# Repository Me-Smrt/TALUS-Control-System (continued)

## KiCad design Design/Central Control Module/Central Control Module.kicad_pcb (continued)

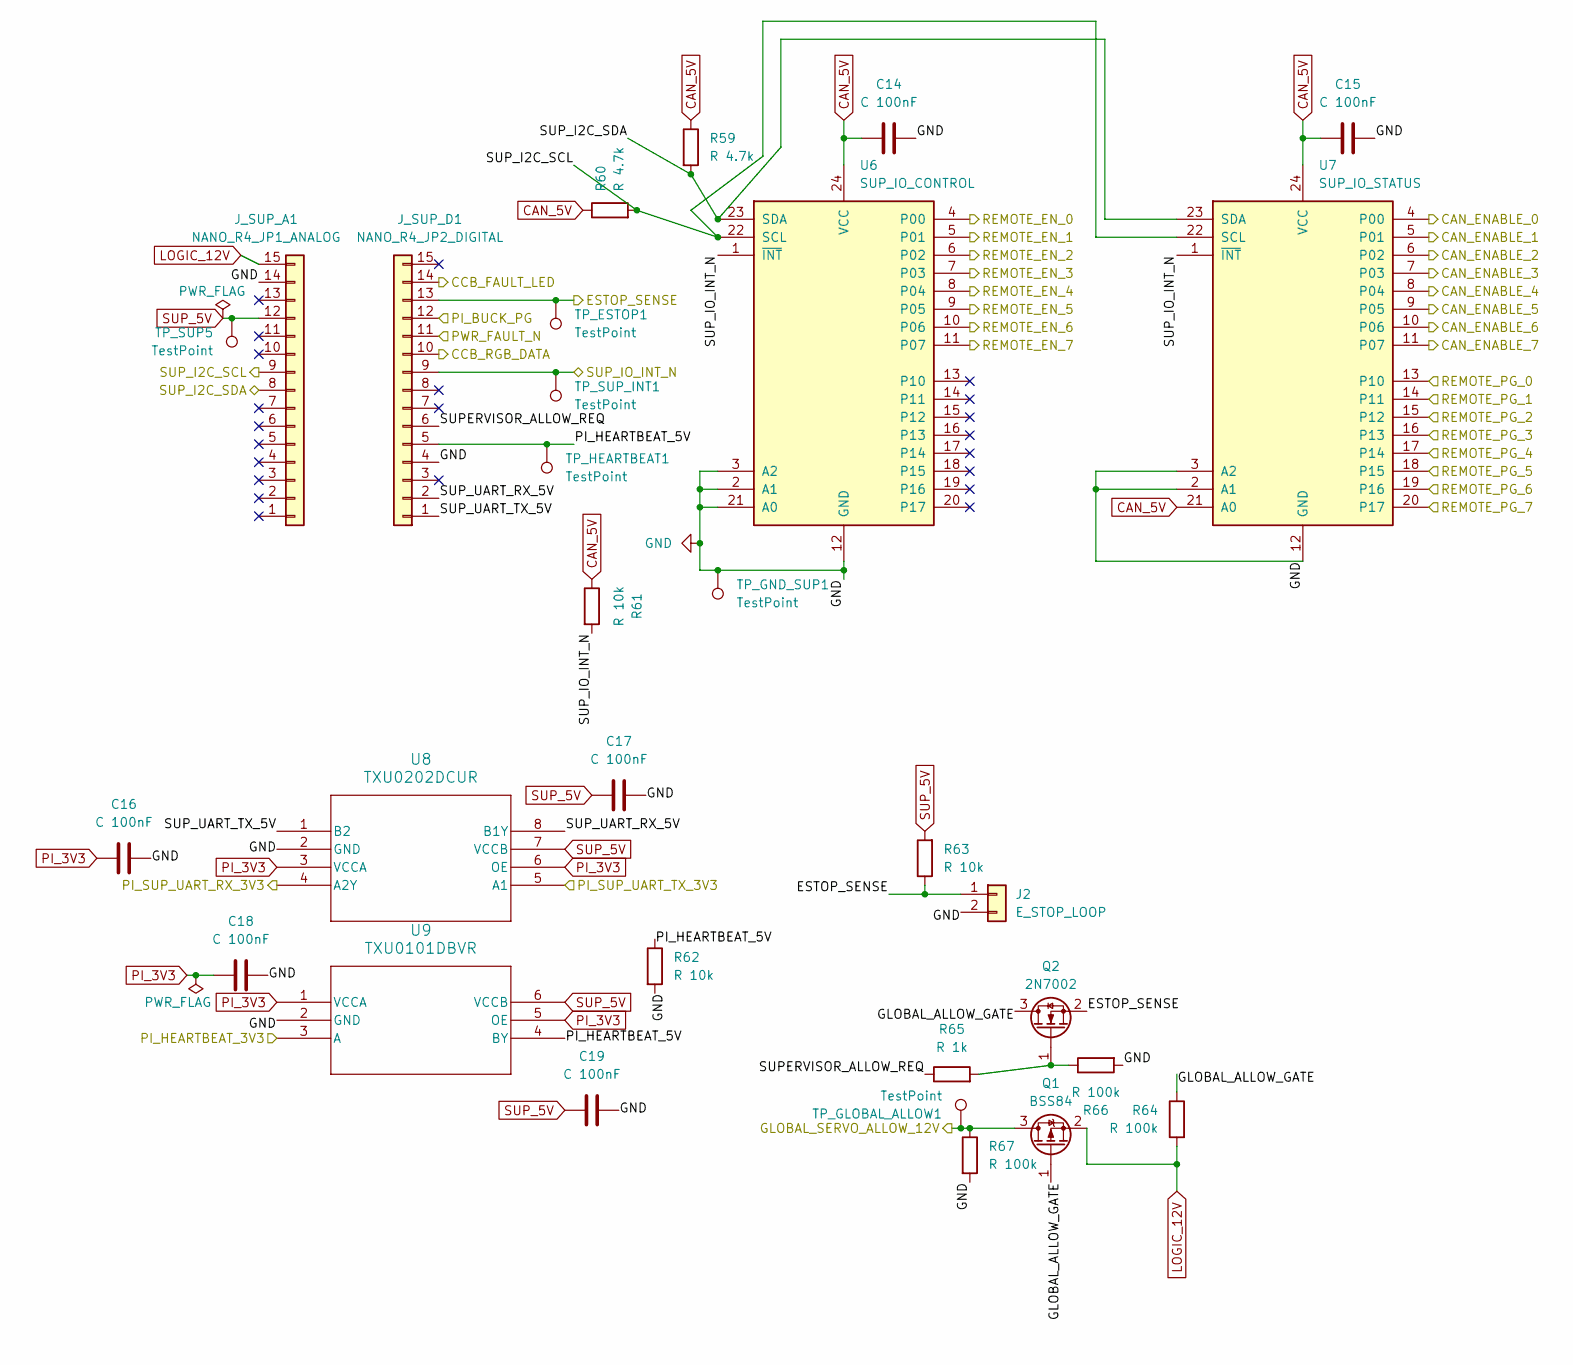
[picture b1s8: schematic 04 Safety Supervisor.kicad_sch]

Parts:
C14, C15, C16, C17, C18, C19: C 100nF; C_0603_1608Metric; MPN GRM188R72A104KA35D
J2: E_STOP_LOOP; PinHeader_1x02_P2.54mm_Vertical; MPN TSW-102-07-G-S
J_SUP_A1: NANO_R4_JP1_ANALOG; PinSocket_1x15_P2.54mm_Vertical; MPN SSW-115-01-S-S
J_SUP_D1: NANO_R4_JP2_DIGITAL; PinSocket_1x15_P2.54mm_Vertical; MPN SSW-115-01-S-S
Q1: BSS84; SOT-23; MPN BSS84LT1G
Q2: 2N7002; SOT-23; MPN 2N7002LT1G
R59, R60: R 4.7k; R_0603_1608Metric; MPN RC0603FR-074K7L
R61, R62, R63: R 10k; R_0603_1608Metric; MPN RC0603FR-0710KL
R64, R66, R67: R 100k; R_0603_1608Metric; MPN RC0603FR-07100KL
R65: R 1k; R_0603_1608Metric; MPN RC0603FR-071KL
TP_ESTOP1: TestPoint; TestPoint_Pad_D1.5mm
TP_GLOBAL_ALLOW1: TestPoint; TestPoint_Pad_D1.5mm
TP_GND_SUP1: TestPoint; TestPoint_Pad_D1.5mm
TP_HEARTBEAT1: TestPoint; TestPoint_Pad_D1.5mm
TP_SUP5: TestPoint; TestPoint_Pad_D1.5mm
TP_SUP_INT1: TestPoint; TestPoint_Pad_D1.5mm
U6: SUP_IO_CONTROL; TSSOP-24_4.4x7.8mm_P0.65mm; MPN TCA9535PWR
U7: SUP_IO_STATUS; TSSOP-24_4.4x7.8mm_P0.65mm; MPN TCA9535PWR
U8: TXU0202DCUR; MPN TXU0202DCUR
U9: TXU0101DBVR; MPN TXU0101DBVR

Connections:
/01 PI Interface/PI_HEARTBEAT_3V3: U9.3 (A); also elsewhere on the board
/01 PI Interface/PI_SUP_UART_RX_3V3: U8.4 (A2Y); also elsewhere on the board
/01 PI Interface/PI_SUP_UART_TX_3V3: U8.5 (A1); also elsewhere on the board
/01 PI Interface/PWR_FAULT_N: J_SUP_D1.11; also elsewhere on the board
/02 Logic Power/PI_BUCK_PG: J_SUP_D1.12; also elsewhere on the board
/04 Safety Supervisor/CCB_FAULT_LED: J_SUP_D1.14; also elsewhere on the board
/04 Safety Supervisor/CCB_RGB_DATA: J_SUP_D1.10; also elsewhere on the board
/04 Safety Supervisor/ESTOP_SENSE: J2.1, J_SUP_D1.13, Q2.2 (S), R63.1, TP_ESTOP1.1 (1_1); also elsewhere on the board
/04 Safety Supervisor/GLOBAL_ALLOW_GATE: Q1.1 (G), Q2.3 (D), R64.1
/04 Safety Supervisor/PI_HEARTBEAT_5V: J_SUP_D1.5, R62.1, TP_HEARTBEAT1.1 (1_1), U9.4 (BY)
/04 Safety Supervisor/REMOTE_EN_0: U6.4 (P00); also elsewhere on the board
/04 Safety Supervisor/REMOTE_EN_1: U6.5 (P01); also elsewhere on the board
/04 Safety Supervisor/REMOTE_EN_2: U6.6 (P02); also elsewhere on the board
/04 Safety Supervisor/REMOTE_EN_3: U6.7 (P03); also elsewhere on the board
/04 Safety Supervisor/REMOTE_EN_4: U6.8 (P04); also elsewhere on the board
/04 Safety Supervisor/REMOTE_EN_5: U6.9 (P05); also elsewhere on the board
/04 Safety Supervisor/REMOTE_EN_6: U6.10 (P06); also elsewhere on the board
/04 Safety Supervisor/REMOTE_EN_7: U6.11 (P07); also elsewhere on the board
/04 Safety Supervisor/REMOTE_PG_0: U7.13 (P10); also elsewhere on the board
/04 Safety Supervisor/REMOTE_PG_1: U7.14 (P11); also elsewhere on the board
/04 Safety Supervisor/REMOTE_PG_2: U7.15 (P12); also elsewhere on the board
/04 Safety Supervisor/REMOTE_PG_3: U7.16 (P13); also elsewhere on the board
/04 Safety Supervisor/REMOTE_PG_4: U7.17 (P14); also elsewhere on the board
/04 Safety Supervisor/REMOTE_PG_5: U7.18 (P15); also elsewhere on the board
/04 Safety Supervisor/REMOTE_PG_6: U7.19 (P16); also elsewhere on the board
/04 Safety Supervisor/REMOTE_PG_7: U7.20 (P17); also elsewhere on the board
/04 Safety Supervisor/SUPERVISOR_ALLOW_REQ: J_SUP_D1.6, R65.1
/04 Safety Supervisor/SUP_I2C_SCL: J_SUP_A1.9, R60.2, U6.22 (SCL), U7.22 (SCL); also elsewhere on the board
/04 Safety Supervisor/SUP_I2C_SDA: J_SUP_A1.8, R59.2, U6.23 (SDA), U7.23 (SDA); also elsewhere on the board
/04 Safety Supervisor/SUP_IO_INT_N: J_SUP_D1.9, R61.2, TP_SUP_INT1.1 (1_1), U6.1 (~INT), U7.1 (~INT); also elsewhere on the board
/04 Safety Supervisor/SUP_UART_RX_5V: J_SUP_D1.2, U8.8 (B1Y)
/04 Safety Supervisor/SUP_UART_TX_5V: J_SUP_D1.1, U8.1 (B2)
/08 Remote_Interfaces/GLOBAL_SERVO_ALLOW_12V: Q1.3 (D), R67.1, TP_GLOBAL_ALLOW1.1 (1_1); also elsewhere on the board
/CAN_ENABLE_0: U7.4 (P00); also elsewhere on the board
/CAN_ENABLE_1: U7.5 (P01); also elsewhere on the board
/CAN_ENABLE_2: U7.6 (P02); also elsewhere on the board
/CAN_ENABLE_3: U7.7 (P03); also elsewhere on the board
/CAN_ENABLE_4: U7.8 (P04); also elsewhere on the board
/CAN_ENABLE_5: U7.9 (P05); also elsewhere on the board
/CAN_ENABLE_6: U7.10 (P06); also elsewhere on the board
/CAN_ENABLE_7: U7.11 (P07); also elsewhere on the board
CAN_5V: C14.1, C15.1, R59.1, R60.1, R61.1, U6.24 (VCC), U7.21 (A0), U7.24 (VCC); also elsewhere on the board
GND: C14.2, C15.2, C16.2, C17.2, C18.2, C19.2, J2.2, J_SUP_A1.14, J_SUP_D1.4, R62.2, R66.2, R67.2, TP_GND_SUP1.1 (1_1), U6.2 (A1), U6.3 (A2), U6.12 (GND), U6.21 (A0), U7.2 (A1), U7.3 (A2), U7.12 (GND), U8.2 (GND), U9.2 (GND); also elsewhere on the board
LOGIC_12V: J_SUP_A1.15, Q1.2 (S), R64.2; also elsewhere on the board
unnamed: Q2.1 (G), R65.2, R66.1
PI_3V3: C16.1, C18.1, U8.3 (VCCA), U8.6 (OE), U9.1 (VCCA), U9.5 (OE); also elsewhere on the board
SUP_5V: C17.1, C19.1, J_SUP_A1.12, R63.2, TP_SUP5.1 (1_1), U8.7 (VCCB), U9.6 (VCCB); also elsewhere on the board

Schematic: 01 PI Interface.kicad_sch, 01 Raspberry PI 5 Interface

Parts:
C1: C 100 nF; C_0603_1608Metric; MPN GRM188R72A104KA35D
JP1: EEPROM_WP; SolderJumper-2_P1.3mm_Open_Pad1.0x1.5mm
J_PI1: Raspberry PI 5 GPIO; PinSocket_2x20_P2.54mm_Vertical_RPi5; MPN SSW-120-01-S-D
R1, R2: R 3.9 kΩ; R_0603_1608Metric; MPN RC0603FR-073K9L
R3: R 1 kΩ; R_0603_1608Metric; MPN RC0603FR-071KL
U1: CAT24C32WI-GT3; SOIC-8_3.9x4.9mm_P1.27mm; MPN CAT24C32WI-GT3

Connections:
/01 PI Interface/CS0_N: J_PI1.24; also elsewhere on the board
/01 PI Interface/CS1_N: J_PI1.26; also elsewhere on the board
/01 PI Interface/CS2_N: J_PI1.7; also elsewhere on the board
/01 PI Interface/CS3_N: J_PI1.11; also elsewhere on the board
/01 PI Interface/CS4_N: J_PI1.13; also elsewhere on the board
/01 PI Interface/CS5_N: J_PI1.15; also elsewhere on the board
/01 PI Interface/CS6_N: J_PI1.16; also elsewhere on the board
/01 PI Interface/CS7_N: J_PI1.18; also elsewhere on the board
/01 PI Interface/EEPROM_WP: JP1.1 (A), R3.2, U1.7 (WP)
/01 PI Interface/ID_SC: J_PI1.28, R2.2, U1.6 (SCL)
/01 PI Interface/ID_SD: J_PI1.27, R1.2, U1.5 (SDA)
/01 PI Interface/INT0_N: J_PI1.22; also elsewhere on the board
/01 PI Interface/INT1_N: J_PI1.29; also elsewhere on the board
/01 PI Interface/INT2_N: J_PI1.31; also elsewhere on the board
/01 PI Interface/INT3_N: J_PI1.32; also elsewhere on the board
/01 PI Interface/INT4_N: J_PI1.33; also elsewhere on the board
/01 PI Interface/INT5_N: J_PI1.35; also elsewhere on the board
/01 PI Interface/INT6_N: J_PI1.36; also elsewhere on the board
/01 PI Interface/INT7_N: J_PI1.37; also elsewhere on the board
/01 PI Interface/PI_HEARTBEAT_3V3: J_PI1.12; also elsewhere on the board
/01 PI Interface/PI_SUP_UART_RX_3V3: J_PI1.10; also elsewhere on the board
/01 PI Interface/PI_SUP_UART_TX_3V3: J_PI1.8; also elsewhere on the board
/01 PI Interface/PWR_FAULT_N: J_PI1.38; also elsewhere on the board
/01 PI Interface/SPI_MISO: J_PI1.21; also elsewhere on the board
/01 PI Interface/SPI_MOSI: J_PI1.19; also elsewhere on the board
/01 PI Interface/SPI_SCK: J_PI1.23; also elsewhere on the board
GND: C1.2, JP1.2 (B), J_PI1.6, J_PI1.9, J_PI1.14, J_PI1.20, J_PI1.25, J_PI1.30, J_PI1.34, J_PI1.39, U1.1 (A0), U1.2 (A1), U1.3 (A2), U1.4 (GND); also elsewhere on the board
PI_3V3: C1.1, J_PI1.1, J_PI1.17, R1.1, R2.1, R3.1, U1.8 (VCC); also elsewhere on the board
PI_5V: J_PI1.2, J_PI1.4; also elsewhere on the board

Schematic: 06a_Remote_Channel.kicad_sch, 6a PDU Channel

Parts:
C20: C 100 nF / 50 V, X7R; C_0603_1608Metric; MPN GRM188R72A104KA35D
C21: C 1 µF / 50 V, X7R; C_1206_3216Metric; MPN GRM31CR71H105KA61L
C22: C 4.7 nF; C_0603_1608Metric; MPN GRM188R71H472KA01D
C23: C 10 nF / 50 V, X7R; C_0603_1608Metric; MPN GRM188R71H103KA01D
C24: C 100 nF; C_0603_1608Metric; MPN GRM188R72A104KA35D
D12: GREEN_LED; LED_0603_1608Metric; MPN LTST-C190KGKT
R68: R 1 kΩ; R_0603_1608Metric; MPN RC0603FR-071KL
R69: R 100 kΩ; R_0603_1608Metric; MPN RC0603FR-07100KL
R70: R 82 Ω; R_0603_1608Metric; MPN RC0603FR-0782RL
R71: R 10 kΩ; R_0603_1608Metric; MPN RC0603FR-0710KL
R72: R 887 Ω; R_0603_1608Metric; MPN RC0603FR-07887RL
R73: R 10k; R_0603_1608Metric; MPN RC0603FR-0710KL
R137: R 4.7k; R_0603_1608Metric; MPN RC0603FR-074K7L
R145: R 910k; R_0603_1608Metric; MPN RC0603FR-07910KL
R153: R 49.9k; R_0603_1608Metric; MPN RC0603FR-0749K9L
U10: TPS259830ONRGER; PARTREV B

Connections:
/04 Safety Supervisor/REMOTE_EN_0: R68.1; also elsewhere on the board
/04 Safety Supervisor/REMOTE_PG_0: R71.2, U10.13 (PG); also elsewhere on the board
/06 Remote Power PDU/PDU_CH0/REMOTE_IMON_RAW: R72.1, R73.1, U10.9 (IMON)
/06 Remote Power PDU/REMOTE_IMON_0: C24.1, R73.2; also elsewhere on the board
/06 Remote Power PDU/REMOTE_VBUS: C20.2, R145.1, U10.1 (IN), U10.2 (IN__1), U10.3 (IN__2), U10.16 (IN__3), U10.25 (IN__4); also elsewhere on the board
/06 Remote Power PDU/REMOTE_VBUS_0: C21.2, R137.2, U10.17 (OUT), U10.18 (OUT__1), U10.19 (OUT__2), U10.20 (OUT__3), U10.21 (OUT__4), U10.22 (OUT__5), U10.23 (OUT__6), U10.24 (OUT__7); also elsewhere on the board
CAN_5V: R71.1; also elsewhere on the board
GND: C20.1, C21.1, C22.2, C23.1, C24.2, D12.1 (K), R69.2, R70.2, R72.2, R153.2, U10.4 (GND), U10.5 (GND__1), U10.10 (RETRY_DLY), U10.14 (GND__2), U10.26 (GND__3); also elsewhere on the board
unnamed: D12.2 (A), R137.1
unnamed: C23.2, U10.15 (DVDT/BGATE)
unnamed: R68.2, R69.1, U10.6 (EN/UVLO)
unnamed: R70.1, U10.8 (ILIM)
unnamed: C22.1, U10.7 (ITIMER)
unnamed: R145.2, R153.1, U10.12 (OVLO)

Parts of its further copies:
C25, C30, C35, C40, C45, C50, C55: C 4.7 nF; C_0603_1608Metric; MPN GRM188R71H472KA01D
C26, C31, C36, C41, C46, C51, C56: C 100 nF; C_0603_1608Metric; MPN GRM188R72A104KA35D
C27, C32, C37, C42, C47, C52, C57: C 100 nF / 50 V, X7R; C_0603_1608Metric; MPN GRM188R72A104KA35D
C28, C33, C38, C43, C48, C53, C58: C 1 µF / 50 V, X7R; C_1206_3216Metric; MPN GRM31CR71H105KA61L
C29, C34, C39, C44, C49, C54, C59: C 10 nF / 50 V, X7R; C_0603_1608Metric; MPN GRM188R71H103KA01D
D13, D14, D15, D16, D17, D18, D19: GREEN_LED; LED_0603_1608Metric; MPN LTST-C190KGKT
R74, R80, R86, R92, R98, R104, R110: R 1 kΩ; R_0603_1608Metric; MPN RC0603FR-071KL
R75, R81, R87, R93, R99, R105, R111: R 100 kΩ; R_0603_1608Metric; MPN RC0603FR-07100KL
R76, R82, R88, R94, R100, R106, R112: R 82 Ω; R_0603_1608Metric; MPN RC0603FR-0782RL
R77, R83, R89, R95, R101, R107, R113: R 10 kΩ; R_0603_1608Metric; MPN RC0603FR-0710KL
R78, R84, R90, R96, R102, R108, R114: R 10k; R_0603_1608Metric; MPN RC0603FR-0710KL
R79, R85, R91, R97, R103, R109, R115: R 887 Ω; R_0603_1608Metric; MPN RC0603FR-07887RL
R138, R139, R140, R141, R142, R143, R144: R 4.7k; R_0603_1608Metric; MPN RC0603FR-074K7L
R146, R147, R148, R149, R150, R151, R152: R 910k; R_0603_1608Metric; MPN RC0603FR-07910KL
R154, R155, R156, R157, R158, R159, R160: R 49.9k; R_0603_1608Metric; MPN RC0603FR-0749K9L
U11, U12, U13, U14, U15, U16, U17: TPS259830ONRGER; PARTREV B

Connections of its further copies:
/04 Safety Supervisor/REMOTE_EN_1: R74.1; also elsewhere on the board
/04 Safety Supervisor/REMOTE_EN_2: R80.1; also elsewhere on the board
/04 Safety Supervisor/REMOTE_EN_3: R86.1; also elsewhere on the board
/04 Safety Supervisor/REMOTE_EN_4: R92.1; also elsewhere on the board
/04 Safety Supervisor/REMOTE_EN_5: R98.1; also elsewhere on the board
/04 Safety Supervisor/REMOTE_EN_6: R104.1; also elsewhere on the board
/04 Safety Supervisor/REMOTE_EN_7: R110.1; also elsewhere on the board
/04 Safety Supervisor/REMOTE_PG_1: R77.2, U11.13 (PG); also elsewhere on the board
/04 Safety Supervisor/REMOTE_PG_2: R83.2, U12.13 (PG); also elsewhere on the board
/04 Safety Supervisor/REMOTE_PG_3: R89.2, U13.13 (PG); also elsewhere on the board
/04 Safety Supervisor/REMOTE_PG_4: R95.2, U14.13 (PG); also elsewhere on the board
/04 Safety Supervisor/REMOTE_PG_5: R101.2, U15.13 (PG); also elsewhere on the board
/04 Safety Supervisor/REMOTE_PG_6: R107.2, U16.13 (PG); also elsewhere on the board
/04 Safety Supervisor/REMOTE_PG_7: R113.2, U17.13 (PG); also elsewhere on the board
/06 Remote Power PDU/PDU_CH1/REMOTE_IMON_RAW: R78.1, R79.1, U11.9 (IMON)
/06 Remote Power PDU/PDU_CH2/REMOTE_IMON_RAW: R84.1, R85.1, U12.9 (IMON)
/06 Remote Power PDU/PDU_CH3/REMOTE_IMON_RAW: R90.1, R91.1, U13.9 (IMON)
/06 Remote Power PDU/PDU_CH4/REMOTE_IMON_RAW: R96.1, R97.1, U14.9 (IMON)
/06 Remote Power PDU/PDU_CH5/REMOTE_IMON_RAW: R102.1, R103.1, U15.9 (IMON)
/06 Remote Power PDU/PDU_CH6/REMOTE_IMON_RAW: R108.1, R109.1, U16.9 (IMON)
/06 Remote Power PDU/PDU_CH7/REMOTE_IMON_RAW: R114.1, R115.1, U17.9 (IMON)
/06 Remote Power PDU/REMOTE_IMON_1: C26.1, R78.2; also elsewhere on the board
/06 Remote Power PDU/REMOTE_IMON_2: C31.1, R84.2; also elsewhere on the board
/06 Remote Power PDU/REMOTE_IMON_3: C36.1, R90.2; also elsewhere on the board
/06 Remote Power PDU/REMOTE_IMON_4: C41.1, R96.2; also elsewhere on the board
/06 Remote Power PDU/REMOTE_IMON_5: C46.1, R102.2; also elsewhere on the board
/06 Remote Power PDU/REMOTE_IMON_6: C51.1, R108.2; also elsewhere on the board
/06 Remote Power PDU/REMOTE_IMON_7: C56.1, R114.2; also elsewhere on the board
/06 Remote Power PDU/REMOTE_VBUS: C27.2, C32.2, C37.2, C42.2, C47.2, C52.2, C57.2, R146.1, R147.1, R148.1, R149.1, R150.1, R151.1, R152.1, U11.1 (IN), U11.2 (IN__1), U11.3 (IN__2), U11.16 (IN__3), U11.25 (IN__4), U12.1 (IN), U12.2 (IN__1), U12.3 (IN__2), U12.16 (IN__3), U12.25 (IN__4), U13.1 (IN), U13.2 (IN__1), U13.3 (IN__2), U13.16 (IN__3), U13.25 (IN__4), U14.1 (IN), U14.2 (IN__1), U14.3 (IN__2), U14.16 (IN__3), U14.25 (IN__4), U15.1 (IN), U15.2 (IN__1), U15.3 (IN__2), U15.16 (IN__3), U15.25 (IN__4), U16.1 (IN), U16.2 (IN__1), U16.3 (IN__2), U16.16 (IN__3), U16.25 (IN__4), U17.1 (IN), U17.2 (IN__1), U17.3 (IN__2), U17.16 (IN__3), U17.25 (IN__4); also elsewhere on the board
/06 Remote Power PDU/REMOTE_VBUS_1: C28.2, R138.2, U11.17 (OUT), U11.18 (OUT__1), U11.19 (OUT__2), U11.20 (OUT__3), U11.21 (OUT__4), U11.22 (OUT__5), U11.23 (OUT__6), U11.24 (OUT__7); also elsewhere on the board
/06 Remote Power PDU/REMOTE_VBUS_2: C33.2, R139.2, U12.17 (OUT), U12.18 (OUT__1), U12.19 (OUT__2), U12.20 (OUT__3), U12.21 (OUT__4), U12.22 (OUT__5), U12.23 (OUT__6), U12.24 (OUT__7); also elsewhere on the board
/06 Remote Power PDU/REMOTE_VBUS_3: C38.2, R140.2, U13.17 (OUT), U13.18 (OUT__1), U13.19 (OUT__2), U13.20 (OUT__3), U13.21 (OUT__4), U13.22 (OUT__5), U13.23 (OUT__6), U13.24 (OUT__7); also elsewhere on the board
/06 Remote Power PDU/REMOTE_VBUS_4: C43.2, R141.2, U14.17 (OUT), U14.18 (OUT__1), U14.19 (OUT__2), U14.20 (OUT__3), U14.21 (OUT__4), U14.22 (OUT__5), U14.23 (OUT__6), U14.24 (OUT__7); also elsewhere on the board
/06 Remote Power PDU/REMOTE_VBUS_5: C48.2, R142.2, U15.17 (OUT), U15.18 (OUT__1), U15.19 (OUT__2), U15.20 (OUT__3), U15.21 (OUT__4), U15.22 (OUT__5), U15.23 (OUT__6), U15.24 (OUT__7); also elsewhere on the board
/06 Remote Power PDU/REMOTE_VBUS_6: C53.2, R143.2, U16.17 (OUT), U16.18 (OUT__1), U16.19 (OUT__2), U16.20 (OUT__3), U16.21 (OUT__4), U16.22 (OUT__5), U16.23 (OUT__6), U16.24 (OUT__7); also elsewhere on the board
/06 Remote Power PDU/REMOTE_VBUS_7: C58.2, R144.2, U17.17 (OUT), U17.18 (OUT__1), U17.19 (OUT__2), U17.20 (OUT__3), U17.21 (OUT__4), U17.22 (OUT__5), U17.23 (OUT__6), U17.24 (OUT__7); also elsewhere on the board
CAN_5V: R77.1, R83.1, R89.1, R95.1, R101.1, R107.1, R113.1; also elsewhere on the board
GND: C25.2, C26.2, C27.1, C28.1, C29.1, C30.2, C31.2, C32.1, C33.1, C34.1, C35.2, C36.2, C37.1, C38.1, C39.1, C40.2, C41.2, C42.1, C43.1, C44.1, C45.2, C46.2, C47.1, C48.1, C49.1, C50.2, C51.2, C52.1, C53.1, C54.1, C55.2, C56.2, C57.1, C58.1, C59.1, D13.1 (K), D14.1 (K), D15.1 (K), D16.1 (K), D17.1 (K), D18.1 (K), D19.1 (K), R75.2, R76.2, R79.2, R81.2, R82.2, R85.2, R87.2, R88.2, R91.2, R93.2, R94.2, R97.2, R99.2, R100.2, R103.2, R105.2, R106.2, R109.2, R111.2, R112.2, R115.2, R154.2, R155.2, R156.2, R157.2, R158.2, R159.2, R160.2, U11.4 (GND), U11.5 (GND__1), U11.10 (RETRY_DLY), U11.14 (GND__2), U11.26 (GND__3), U12.4 (GND), U12.5 (GND__1), U12.10 (RETRY_DLY), U12.14 (GND__2), U12.26 (GND__3), U13.4 (GND), U13.5 (GND__1), U13.10 (RETRY_DLY), U13.14 (GND__2), U13.26 (GND__3), U14.4 (GND), U14.5 (GND__1), U14.10 (RETRY_DLY), U14.14 (GND__2), U14.26 (GND__3), U15.4 (GND), U15.5 (GND__1), U15.10 (RETRY_DLY), U15.14 (GND__2), U15.26 (GND__3), U16.4 (GND), U16.5 (GND__1), U16.10 (RETRY_DLY), U16.14 (GND__2), U16.26 (GND__3), U17.4 (GND), U17.5 (GND__1), U17.10 (RETRY_DLY), U17.14 (GND__2), U17.26 (GND__3); also elsewhere on the board
unnamed: D13.2 (A), R138.1
unnamed: D14.2 (A), R139.1
unnamed: D15.2 (A), R140.1
unnamed: D16.2 (A), R141.1
unnamed: D17.2 (A), R142.1
unnamed: D18.2 (A), R143.1
unnamed: D19.2 (A), R144.1
unnamed: C29.2, U11.15 (DVDT/BGATE)
unnamed: R74.2, R75.1, U11.6 (EN/UVLO)
unnamed: R76.1, U11.8 (ILIM)
unnamed: C25.1, U11.7 (ITIMER)
unnamed: R146.2, R154.1, U11.12 (OVLO)
unnamed: C34.2, U12.15 (DVDT/BGATE)
unnamed: R80.2, R81.1, U12.6 (EN/UVLO)
unnamed: R82.1, U12.8 (ILIM)
unnamed: C30.1, U12.7 (ITIMER)
unnamed: R147.2, R155.1, U12.12 (OVLO)
unnamed: C39.2, U13.15 (DVDT/BGATE)
unnamed: R86.2, R87.1, U13.6 (EN/UVLO)
unnamed: R88.1, U13.8 (ILIM)
unnamed: C35.1, U13.7 (ITIMER)
unnamed: R148.2, R156.1, U13.12 (OVLO)
unnamed: C44.2, U14.15 (DVDT/BGATE)
unnamed: R92.2, R93.1, U14.6 (EN/UVLO)
unnamed: R94.1, U14.8 (ILIM)
unnamed: C40.1, U14.7 (ITIMER)
unnamed: R149.2, R157.1, U14.12 (OVLO)
unnamed: C49.2, U15.15 (DVDT/BGATE)
unnamed: R98.2, R99.1, U15.6 (EN/UVLO)
unnamed: R100.1, U15.8 (ILIM)
unnamed: C45.1, U15.7 (ITIMER)
unnamed: R150.2, R158.1, U15.12 (OVLO)
unnamed: C54.2, U16.15 (DVDT/BGATE)
unnamed: R104.2, R105.1, U16.6 (EN/UVLO)
unnamed: R106.1, U16.8 (ILIM)
unnamed: C50.1, U16.7 (ITIMER)
unnamed: R151.2, R159.1, U16.12 (OVLO)
unnamed: C59.2, U17.15 (DVDT/BGATE)
unnamed: R110.2, R111.1, U17.6 (EN/UVLO)
unnamed: R112.1, U17.8 (ILIM)
unnamed: C55.1, U17.7 (ITIMER)
unnamed: R152.2, R160.1, U17.12 (OVLO)

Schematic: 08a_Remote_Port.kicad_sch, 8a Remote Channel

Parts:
CR1: PESD2CAN24DBZRQ1; MPN ESD2CAN24DBZRQ1
J3: 0438100003; CONN_SD-43810-011_08_CLIP_MOL; MPN 0438100003
R116: R 1k; R_0603_1608Metric; MPN RC0603FR-071KL

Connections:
/06 Remote Power PDU/REMOTE_VBUS_0: J3.3, J3.5, J3.7; also elsewhere on the board
/08 Remote_Interfaces/GLOBAL_SERVO_ALLOW_12V: R116.1; also elsewhere on the board
/08 Remote_Interfaces/REMOTE_CH0/CAN_H: CR1.1, J3.1; also elsewhere on the board
/08 Remote_Interfaces/REMOTE_CH0/CAN_L: CR1.2, J3.2; also elsewhere on the board
GND: CR1.3, J3.4, J3.6; also elsewhere on the board
unnamed: J3.8, R116.2

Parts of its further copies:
CR2, CR3, CR4, CR5, CR6, CR7, CR8: PESD2CAN24DBZRQ1; MPN ESD2CAN24DBZRQ1
J4, J5, J6, J7, J8, J9, J10: 0438100003; CONN_SD-43810-011_08_CLIP_MOL; MPN 0438100003
R117, R118, R119, R120, R121, R122, R123: R 1k; R_0603_1608Metric; MPN RC0603FR-071KL

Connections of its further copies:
/06 Remote Power PDU/REMOTE_VBUS_1: J4.3, J4.5, J4.7; also elsewhere on the board
/06 Remote Power PDU/REMOTE_VBUS_2: J5.3, J5.5, J5.7; also elsewhere on the board
/06 Remote Power PDU/REMOTE_VBUS_3: J6.3, J6.5, J6.7; also elsewhere on the board
/06 Remote Power PDU/REMOTE_VBUS_4: J7.3, J7.5, J7.7; also elsewhere on the board
/06 Remote Power PDU/REMOTE_VBUS_5: J8.3, J8.5, J8.7; also elsewhere on the board
/06 Remote Power PDU/REMOTE_VBUS_6: J9.3, J9.5, J9.7; also elsewhere on the board
/06 Remote Power PDU/REMOTE_VBUS_7: J10.3, J10.5, J10.7; also elsewhere on the board
/08 Remote_Interfaces/GLOBAL_SERVO_ALLOW_12V: R117.1, R118.1, R119.1, R120.1, R121.1, R122.1, R123.1; also elsewhere on the board
/08 Remote_Interfaces/REMOTE_CH1/CAN_H: CR2.1, J4.1; also elsewhere on the board
/08 Remote_Interfaces/REMOTE_CH1/CAN_L: CR2.2, J4.2; also elsewhere on the board
/08 Remote_Interfaces/REMOTE_CH2/CAN_H: CR3.1, J5.1; also elsewhere on the board
/08 Remote_Interfaces/REMOTE_CH2/CAN_L: CR3.2, J5.2; also elsewhere on the board
/08 Remote_Interfaces/REMOTE_CH3/CAN_H: CR4.1, J6.1; also elsewhere on the board
/08 Remote_Interfaces/REMOTE_CH3/CAN_L: CR4.2, J6.2; also elsewhere on the board
/08 Remote_Interfaces/REMOTE_CH4/CAN_H: CR5.1, J7.1; also elsewhere on the board
/08 Remote_Interfaces/REMOTE_CH4/CAN_L: CR5.2, J7.2; also elsewhere on the board
/08 Remote_Interfaces/REMOTE_CH5/CAN_H: CR6.1, J8.1; also elsewhere on the board
/08 Remote_Interfaces/REMOTE_CH5/CAN_L: CR6.2, J8.2; also elsewhere on the board
/08 Remote_Interfaces/REMOTE_CH6/CAN_H: CR7.1, J9.1; also elsewhere on the board
/08 Remote_Interfaces/REMOTE_CH6/CAN_L: CR7.2, J9.2; also elsewhere on the board
/08 Remote_Interfaces/REMOTE_CH7/CAN_H: CR8.1, J10.1; also elsewhere on the board
/08 Remote_Interfaces/REMOTE_CH7/CAN_L: CR8.2, J10.2; also elsewhere on the board
GND: CR2.3, CR3.3, CR4.3, CR5.3, CR6.3, CR7.3, CR8.3, J4.4, J4.6, J5.4, J5.6, J6.4, J6.6, J7.4, J7.6, J8.4, J8.6, J9.4, J9.6, J10.4, J10.6; also elsewhere on the board
unnamed: J4.8, R117.2
unnamed: J5.8, R118.2
unnamed: J6.8, R119.2
unnamed: J7.8, R120.2
unnamed: J8.8, R121.2
unnamed: J9.8, R122.2
unnamed: J10.8, R123.2

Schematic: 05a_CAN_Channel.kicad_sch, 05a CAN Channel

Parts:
C77, C78, C79, C126: C 100nF; C_0603_1608Metric; MPN GRM188R72A104KA35D
C80, C81: C 12pF; C_0603_1608Metric; MPN C1608C0G1H120J080AA
Q15: 2N7002; SOT-23; MPN 2N7002LT1G
R164, R165, R168: R 10k; R_0603_1608Metric; MPN RC0603FR-0710KL
R166: R 1k; R_0603_1608Metric; MPN RC0603FR-071KL
R167: R 100k; R_0603_1608Metric; MPN RC0603FR-07100KL
R170: R 33Ω; R_0603_1608Metric; MPN RC0603FR-0733RL
R192: R 120Ω; R_0603_1608Metric; MPN RC0603FR-07120RL
U21: MCP25625-E/SS; SSOP-28_5.3x10.2mm_P0.65mm; MPN MCP25625-E/SS
Y1: ABM8W-20.0000MHZ-8-D1X-T3; XTAL_ABM8W-20.0000MHZ-8-D1X-T3; PARTREV 08.09.2018

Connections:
/01 PI Interface/INT0_N: U21.13 (~INT); also elsewhere on the board
/01 PI Interface/SPI_MISO: R170.1; also elsewhere on the board
/05 CAN Slots/CS0_SLOT_N: R164.2, U21.17 (~CS); also elsewhere on the board
/05 CAN Slots/SPI_MOSI_BUS: U21.15 (SI); also elsewhere on the board
/05 CAN Slots/SPI_SCK_BUS: U21.14 (SCK); also elsewhere on the board
/08 Remote_Interfaces/REMOTE_CH0/CAN_H: R192.1, U21.4 (CANH); also elsewhere on the board
/08 Remote_Interfaces/REMOTE_CH0/CAN_L: R192.2, U21.3 (CANL); also elsewhere on the board
/CAN_ENABLE_0: R166.1; also elsewhere on the board
CAN_5V: C79.1, U21.27 (V_{DDA}); also elsewhere on the board
GND: C77.2, C78.2, C79.2, C80.2, C81.2, C126.2, Q15.2 (S), R167.2, U21.10 (GND), U21.26 (V_{SS}), Y1.2 (GND), Y1.4 (GND__1); also elsewhere on the board
unnamed: Q15.3 (D), R165.2, U21.5 (STBY)
unnamed: Q15.1 (G), R166.2, R167.1
unnamed: C80.1, U21.9 (OSC1), Y1.3
unnamed: C81.1, U21.8 (OSC2), Y1.1
unnamed: U21.21 (RxCAN), U21.28 (R_{XD})
unnamed: R170.2, U21.16 (SO)
unnamed: U21.20 (TxCAN), U21.24 (T_{XD})
unnamed: C126.1, R168.2, U21.18 (~RESET)
PI_3V3: C77.1, C78.1, R164.1, R165.1, R168.1, U21.1 (V_{IO}), U21.19 (V_{DD}); also elsewhere on the board

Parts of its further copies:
C91, C92, C93, C96, C97, C98, C101, C102, C103, C106, C107, C108, C111, C112, C113, C116, C117, C118, C121, C122, C123, C127, C128, C129, C130, C131, C132, C133: C 100nF; C_0603_1608Metric; MPN GRM188R72A104KA35D
C94, C95, C99, C100, C104, C105, C109, C110, C114, C115, C119, C120, C124, C125: C 12pF; C_0603_1608Metric; MPN C1608C0G1H120J080AA
Q16, Q17, Q18, Q19, Q20, Q21, Q22: 2N7002; SOT-23; MPN 2N7002LT1G
R171, R172, R173, R174, R175, R176, R177: R 33Ω; R_0603_1608Metric; MPN RC0603FR-0733RL
R193, R200, R207, R214, R221, R228, R235: R 1k; R_0603_1608Metric; MPN RC0603FR-071KL
R194, R201, R208, R215, R222, R229, R236: R 100k; R_0603_1608Metric; MPN RC0603FR-07100KL
R195, R196, R197, R202, R203, R204, R209, R210, R211, R216, R217, R218, R223, R224, R225, R230, R231, R232, R237, R238, R239: R 10k; R_0603_1608Metric; MPN RC0603FR-0710KL
R199, R206, R213, R220, R227, R234, R241: R 120Ω; R_0603_1608Metric; MPN RC0603FR-07120RL
U22, U23, U24, U25, U26, U27, U28: MCP25625-E/SS; SSOP-28_5.3x10.2mm_P0.65mm; MPN MCP25625-E/SS
Y2, Y3, Y4, Y5, Y6, Y7, Y8: ABM8W-20.0000MHZ-8-D1X-T3; XTAL_ABM8W-20.0000MHZ-8-D1X-T3; PARTREV 08.09.2018

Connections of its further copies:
/01 PI Interface/INT1_N: U22.13 (~INT); also elsewhere on the board
/01 PI Interface/INT2_N: U23.13 (~INT); also elsewhere on the board
/01 PI Interface/INT3_N: U24.13 (~INT); also elsewhere on the board
/01 PI Interface/INT4_N: U25.13 (~INT); also elsewhere on the board
/01 PI Interface/INT5_N: U26.13 (~INT); also elsewhere on the board
/01 PI Interface/INT6_N: U27.13 (~INT); also elsewhere on the board
/01 PI Interface/INT7_N: U28.13 (~INT); also elsewhere on the board
/01 PI Interface/SPI_MISO: R171.1, R172.1, R173.1, R174.1, R175.1, R176.1, R177.1; also elsewhere on the board
/05 CAN Slots/CS1_SLOT_N: R196.2, U22.17 (~CS); also elsewhere on the board
/05 CAN Slots/CS2_SLOT_N: R203.2, U23.17 (~CS); also elsewhere on the board
/05 CAN Slots/CS3_SLOT_N: R210.2, U24.17 (~CS); also elsewhere on the board
/05 CAN Slots/CS4_SLOT_N: R217.2, U25.17 (~CS); also elsewhere on the board
/05 CAN Slots/CS5_SLOT_N: R224.2, U26.17 (~CS); also elsewhere on the board
/05 CAN Slots/CS6_SLOT_N: R231.2, U27.17 (~CS); also elsewhere on the board
/05 CAN Slots/CS7_SLOT_N: R238.2, U28.17 (~CS); also elsewhere on the board
/05 CAN Slots/SPI_MOSI_BUS: U22.15 (SI), U23.15 (SI), U24.15 (SI), U25.15 (SI), U26.15 (SI), U27.15 (SI), U28.15 (SI); also elsewhere on the board
/05 CAN Slots/SPI_SCK_BUS: U22.14 (SCK), U23.14 (SCK), U24.14 (SCK), U25.14 (SCK), U26.14 (SCK), U27.14 (SCK), U28.14 (SCK); also elsewhere on the board
/08 Remote_Interfaces/REMOTE_CH1/CAN_H: R199.1, U22.4 (CANH); also elsewhere on the board
/08 Remote_Interfaces/REMOTE_CH1/CAN_L: R199.2, U22.3 (CANL); also elsewhere on the board
/08 Remote_Interfaces/REMOTE_CH2/CAN_H: R206.1, U23.4 (CANH); also elsewhere on the board
/08 Remote_Interfaces/REMOTE_CH2/CAN_L: R206.2, U23.3 (CANL); also elsewhere on the board
/08 Remote_Interfaces/REMOTE_CH3/CAN_H: R213.1, U24.4 (CANH); also elsewhere on the board
/08 Remote_Interfaces/REMOTE_CH3/CAN_L: R213.2, U24.3 (CANL); also elsewhere on the board
/08 Remote_Interfaces/REMOTE_CH4/CAN_H: R220.1, U25.4 (CANH); also elsewhere on the board
/08 Remote_Interfaces/REMOTE_CH4/CAN_L: R220.2, U25.3 (CANL); also elsewhere on the board
/08 Remote_Interfaces/REMOTE_CH5/CAN_H: R227.1, U26.4 (CANH); also elsewhere on the board
/08 Remote_Interfaces/REMOTE_CH5/CAN_L: R227.2, U26.3 (CANL); also elsewhere on the board
/08 Remote_Interfaces/REMOTE_CH6/CAN_H: R234.1, U27.4 (CANH); also elsewhere on the board
/08 Remote_Interfaces/REMOTE_CH6/CAN_L: R234.2, U27.3 (CANL); also elsewhere on the board
/08 Remote_Interfaces/REMOTE_CH7/CAN_H: R241.1, U28.4 (CANH); also elsewhere on the board
/08 Remote_Interfaces/REMOTE_CH7/CAN_L: R241.2, U28.3 (CANL); also elsewhere on the board
/CAN_ENABLE_1: R193.1; also elsewhere on the board
/CAN_ENABLE_2: R200.1; also elsewhere on the board
/CAN_ENABLE_3: R207.1; also elsewhere on the board
/CAN_ENABLE_4: R214.1; also elsewhere on the board
/CAN_ENABLE_5: R221.1; also elsewhere on the board
/CAN_ENABLE_6: R228.1; also elsewhere on the board
/CAN_ENABLE_7: R235.1; also elsewhere on the board
CAN_5V: C93.1, C98.1, C103.1, C108.1, C113.1, C118.1, C123.1, U22.27 (V_{DDA}), U23.27 (V_{DDA}), U24.27 (V_{DDA}), U25.27 (V_{DDA}), U26.27 (V_{DDA}), U27.27 (V_{DDA}), U28.27 (V_{DDA}); also elsewhere on the board
GND: C91.2, C92.2, C93.2, C94.2, C95.2, C96.2, C97.2, C98.2, C99.2, C100.2, C101.2, C102.2, C103.2, C104.2, C105.2, C106.2, C107.2, C108.2, C109.2, C110.2, C111.2, C112.2, C113.2, C114.2, C115.2, C116.2, C117.2, C118.2, C119.2, C120.2, C121.2, C122.2, C123.2, C124.2, C125.2, C127.2, C128.2, C129.2, C130.2, C131.2, C132.2, C133.2, Q16.2 (S), Q17.2 (S), Q18.2 (S), Q19.2 (S), Q20.2 (S), Q21.2 (S), Q22.2 (S), R194.2, R201.2, R208.2, R215.2, R222.2, R229.2, R236.2, U22.10 (GND), U22.26 (V_{SS}), U23.10 (GND), U23.26 (V_{SS}), U24.10 (GND), U24.26 (V_{SS}), U25.10 (GND), U25.26 (V_{SS}), U26.10 (GND), U26.26 (V_{SS}), U27.10 (GND), U27.26 (V_{SS}), U28.10 (GND), U28.26 (V_{SS}), Y2.2 (GND), Y2.4 (GND__1), Y3.2 (GND), Y3.4 (GND__1), Y4.2 (GND), Y4.4 (GND__1), Y5.2 (GND), Y5.4 (GND__1), Y6.2 (GND), Y6.4 (GND__1), Y7.2 (GND), Y7.4 (GND__1), Y8.2 (GND), Y8.4 (GND__1); also elsewhere on the board
unnamed: Q16.3 (D), R195.2, U22.5 (STBY)
unnamed: Q16.1 (G), R193.2, R194.1
unnamed: Q17.3 (D), R202.2, U23.5 (STBY)
unnamed: Q17.1 (G), R200.2, R201.1
unnamed: Q18.3 (D), R209.2, U24.5 (STBY)
unnamed: Q18.1 (G), R207.2, R208.1
unnamed: Q19.3 (D), R216.2, U25.5 (STBY)
unnamed: Q19.1 (G), R214.2, R215.1
unnamed: Q20.3 (D), R223.2, U26.5 (STBY)
unnamed: Q20.1 (G), R221.2, R222.1
unnamed: Q21.3 (D), R230.2, U27.5 (STBY)
unnamed: Q21.1 (G), R228.2, R229.1
unnamed: Q22.3 (D), R237.2, U28.5 (STBY)
unnamed: Q22.1 (G), R235.2, R236.1
unnamed: C94.1, U22.9 (OSC1), Y2.3
unnamed: C95.1, U22.8 (OSC2), Y2.1
unnamed: U22.21 (RxCAN), U22.28 (R_{XD})
unnamed: R171.2, U22.16 (SO)
unnamed: U22.20 (TxCAN), U22.24 (T_{XD})
unnamed: C127.1, R197.2, U22.18 (~RESET)
unnamed: C99.1, U23.9 (OSC1), Y3.3
unnamed: C100.1, U23.8 (OSC2), Y3.1
unnamed: U23.21 (RxCAN), U23.28 (R_{XD})
unnamed: R172.2, U23.16 (SO)
unnamed: U23.20 (TxCAN), U23.24 (T_{XD})
unnamed: C128.1, R204.2, U23.18 (~RESET)
unnamed: C104.1, U24.9 (OSC1), Y4.3
unnamed: C105.1, U24.8 (OSC2), Y4.1
unnamed: U24.21 (RxCAN), U24.28 (R_{XD})
unnamed: R173.2, U24.16 (SO)
unnamed: U24.20 (TxCAN), U24.24 (T_{XD})
unnamed: C129.1, R211.2, U24.18 (~RESET)
unnamed: C109.1, U25.9 (OSC1), Y5.3
unnamed: C110.1, U25.8 (OSC2), Y5.1
unnamed: U25.21 (RxCAN), U25.28 (R_{XD})
unnamed: R174.2, U25.16 (SO)
unnamed: U25.20 (TxCAN), U25.24 (T_{XD})
unnamed: C130.1, R218.2, U25.18 (~RESET)
unnamed: C114.1, U26.9 (OSC1), Y6.3
unnamed: C115.1, U26.8 (OSC2), Y6.1
unnamed: U26.21 (RxCAN), U26.28 (R_{XD})
unnamed: R175.2, U26.16 (SO)
unnamed: U26.20 (TxCAN), U26.24 (T_{XD})
unnamed: C131.1, R225.2, U26.18 (~RESET)
unnamed: C119.1, U27.9 (OSC1), Y7.3
unnamed: C120.1, U27.8 (OSC2), Y7.1
unnamed: U27.21 (RxCAN), U27.28 (R_{XD})
unnamed: R176.2, U27.16 (SO)
unnamed: U27.20 (TxCAN), U27.24 (T_{XD})
unnamed: C132.1, R232.2, U27.18 (~RESET)
unnamed: C124.1, U28.9 (OSC1), Y8.3
unnamed: C125.1, U28.8 (OSC2), Y8.1
unnamed: U28.21 (RxCAN), U28.28 (R_{XD})
unnamed: R177.2, U28.16 (SO)
unnamed: U28.20 (TxCAN), U28.24 (T_{XD})
unnamed: C133.1, R239.2, U28.18 (~RESET)
PI_3V3: C91.1, C92.1, C96.1, C97.1, C101.1, C102.1, C106.1, C107.1, C111.1, C112.1, C116.1, C117.1, C121.1, C122.1, R195.1, R196.1, R197.1, R202.1, R203.1, R204.1, R209.1, R210.1, R211.1, R216.1, R217.1, R218.1, R223.1, R224.1, R225.1, R230.1, R231.1, R232.1, R237.1, R238.1, R239.1, U22.1 (V_{IO}), U22.19 (V_{DD}), U23.1 (V_{IO}), U23.19 (V_{DD}), U24.1 (V_{IO}), U24.19 (V_{DD}), U25.1 (V_{IO}), U25.19 (V_{DD}), U26.1 (V_{IO}), U26.19 (V_{DD}), U27.1 (V_{IO}), U27.19 (V_{DD}), U28.1 (V_{IO}), U28.19 (V_{DD}); also elsewhere on the board

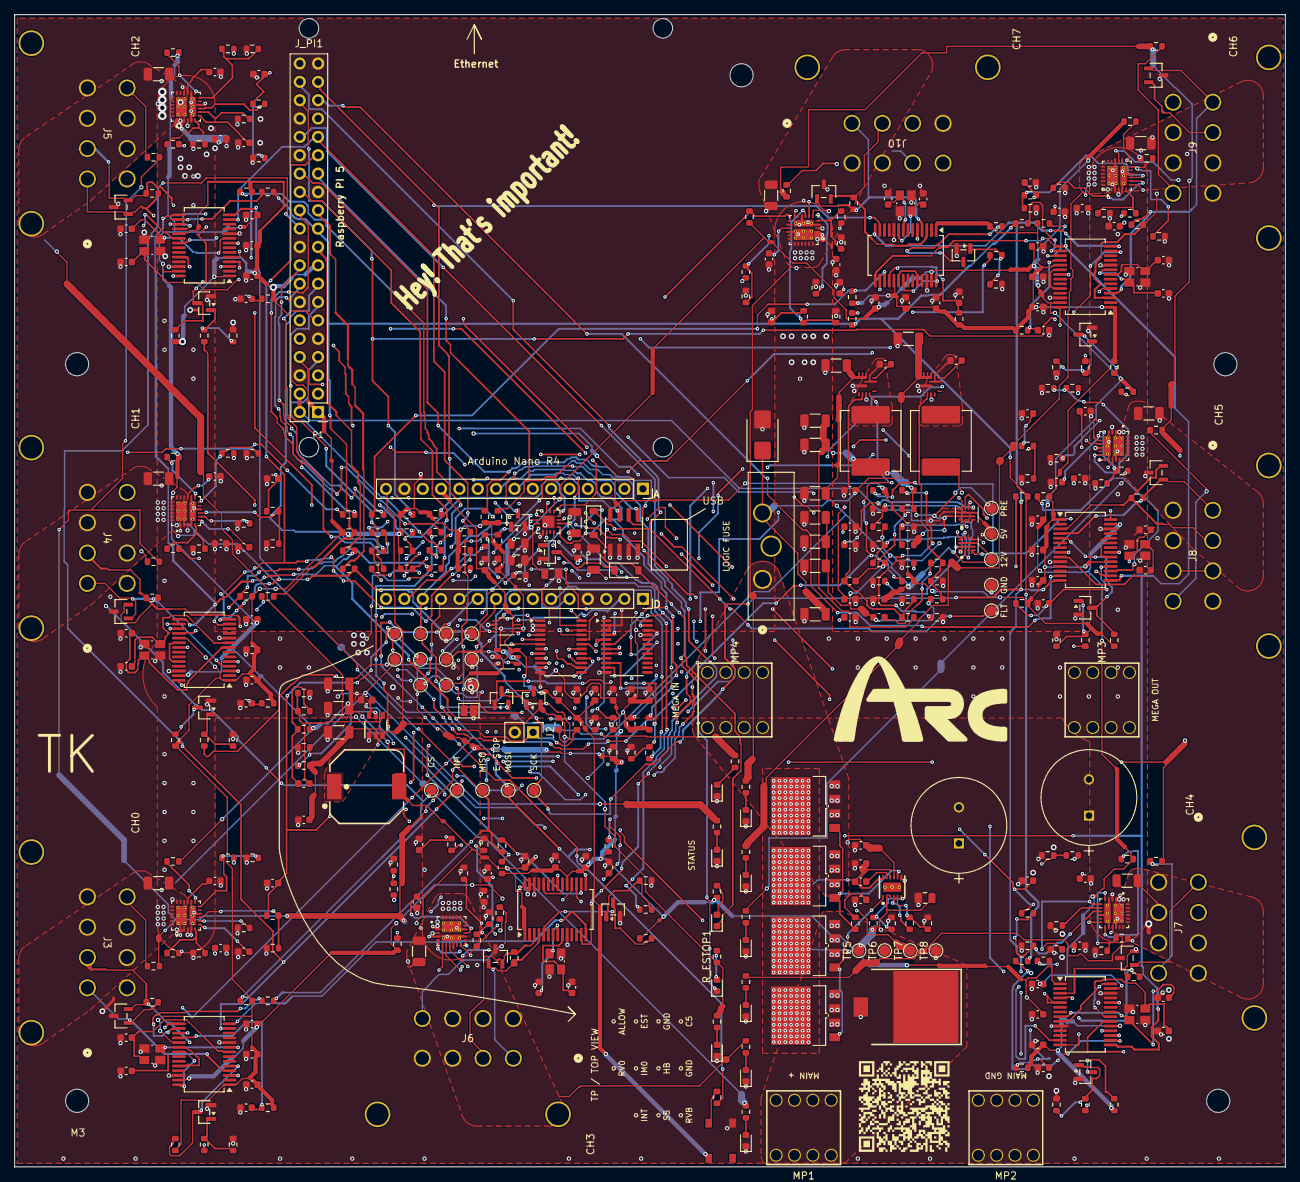
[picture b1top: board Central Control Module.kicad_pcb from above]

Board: 4 copper layers, 176.0 x 159.6 mm, 462 parts (0 on the bottom side), 286 nets.
